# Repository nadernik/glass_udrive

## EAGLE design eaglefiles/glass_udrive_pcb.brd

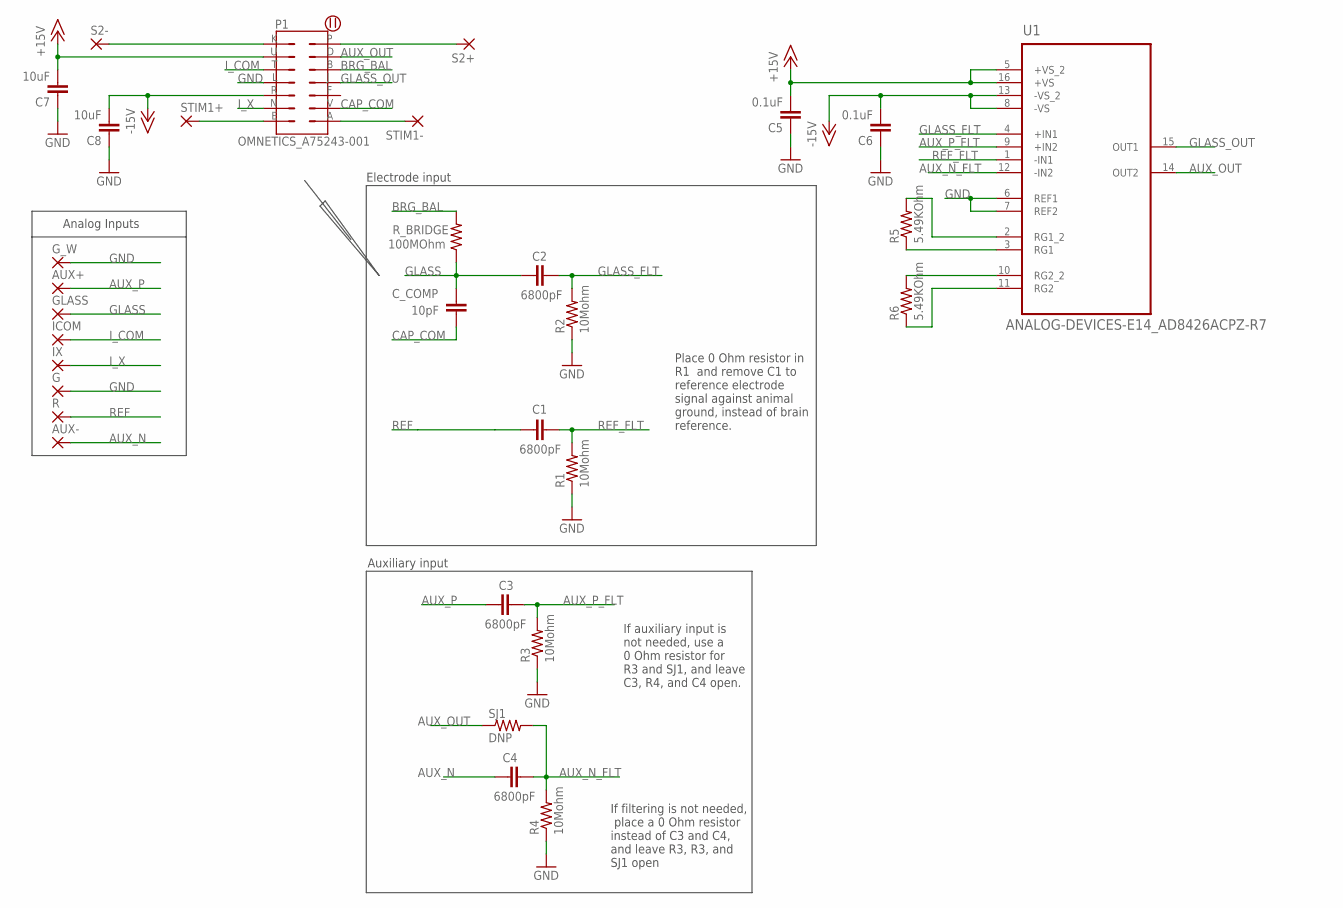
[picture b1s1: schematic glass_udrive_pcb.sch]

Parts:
AUX+: THROUGH-HOLE-30MIL/15MIL; 30MIL/15MIL
AUX-: THROUGH-HOLE-30MIL/15MIL; 30MIL/15MIL
C1, C2, C3, C4: 6800pF; 0201
C5, C6: 0.1uF; 0201
C7, C8: 10uF; 0603
C_COMP: 10pF; 0402
G: THROUGH-HOLE-30MIL/15MIL; 30MIL/15MIL
GLASS: THROUGH-HOLE-30MIL/15MIL; 30MIL/15MIL
G_W: THROUGH-HOLE-30MIL/15MIL; 30MIL/15MIL
ICOM: THROUGH-HOLE-30MIL/15MIL; 30MIL/15MIL
IX: THROUGH-HOLE-30MIL/15MIL; 30MIL/15MIL
P1: OMNETICS_A75243-001
R: THROUGH-HOLE-30MIL/15MIL; 30MIL/15MIL
R1, R2, R3, R4: 10Mohm; 0201
R5, R6: 5.49KOhm; 0201
R_BRIDGE: 100MOhm; 0402
S2+, S2-: THROUGH-HOLE-30MIL/15MIL; 30MIL/15MIL
SJ1: DNP; 0201
STIM1+, STIM1-: THROUGH-HOLE-30MIL/15MIL; 30MIL/15MIL
U1: ANALOG-DEVICES-E14_AD8426ACPZ-R7; ANALOG-DEVICES-E14_QFN65P400X400X100-16N

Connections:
+15V: C5.2, C7.2, P1.U, U1.5 (+VS_2), U1.16 (+VS)
-15V: C6.2, C8.2, P1.R, U1.8 (-VS), U1.13 (-VS_2)
AUX_N: AUX-.P$1, C4.1
AUX_N_FLT: C4.2, R4.2, SJ1.2, U1.12 (-IN2)
AUX_OUT: P1.D, SJ1.1, U1.14 (OUT2)
AUX_P: AUX+.P$1, C3.1
AUX_P_FLT: C3.2, R3.2, U1.9 (+IN2)
BRG_BAL: P1.B, R_BRIDGE.2
CAP_COM: C_COMP.2, P1.V
GLASS: C2.1, C_COMP.1, GLASS.P$1, R_BRIDGE.1
GLASS_FLT: C2.2, R2.2, U1.4 (+IN1)
GLASS_OUT: P1.J, U1.15 (OUT1)
GND: C5.1, C6.1, C7.1, C8.1, G.P$1, G_W.P$1, P1.L, R1.1, R2.1, R3.1, R4.1, U1.6 (REF1), U1.7 (REF2)
I_COM: ICOM.P$1, P1.T
I_X: IX.P$1, P1.N
unnamed: R5.2, U1.2 (RG1_2)
unnamed: R5.1, U1.3 (RG1)
unnamed: R6.2, U1.10 (RG2_2)
unnamed: R6.1, U1.11 (RG2)
REF: C1.1, R.P$1
REF_FLT: C1.2, R1.2, U1.1 (-IN1)
STIM1_N: P1.A, STIM1-.P$1
STIM1_P: P1.E, STIM1+.P$1
STIM2_N: P1.P, S2+.P$1
STIM2_P: P1.K, S2-.P$1

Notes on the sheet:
Analog Inputs
Electrode input
Auxiliary input
Place 0 Ohm resistor in R1 and remove C1 to reference electrode signal against animal ground, instead of brain reference.
If auxiliary input is not needed, use a 0 Ohm resistor for R3 and SJ1, and leave C3, R4, and C4 open.
If filtering is not needed, place a 0 Ohm resistor instead of C3 and C4, and leave R3, R3, and SJ1 open

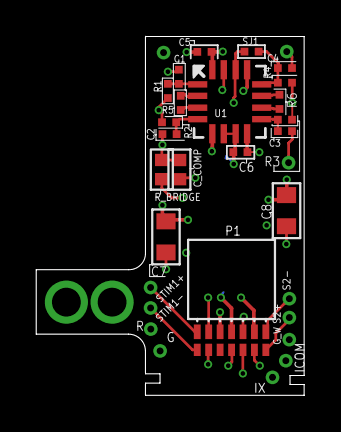
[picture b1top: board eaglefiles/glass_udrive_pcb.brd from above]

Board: 4 copper layers, 14.9 x 19.9 mm, 31 parts (0 on the bottom side), 25 nets.

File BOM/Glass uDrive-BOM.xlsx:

Part on PCB | QTY | Value | Device | Package | Description | Use | SUPPLIER | partNo | link
U1 | 1.0 | AD8224ACPZ-R7 | AD8224 | QFN65P400X400X100-16N | IC OPAMP INSTR 1.5MHZ 16LFCSP-Hidden pad | Wide Supply Range, Rail-to-Rail Output Instrumentation Amplifier | Analog Devices | AD8224HBCPZ-R7CT-ND | https://www.digikey.com/short/jmmmcj
P1 | 1.0 | A75243-001 | A75243-001 | OMNETICS_A75243-001 |  | 14 pin nano, male | Omnetics | A75243-001
R_BRIDGE | 1.0 | 100MOhm | R_0402 | 402.0 | RES 100M OHM 5% 1/16W 0402 | Resistor for bridge balance circuit | Stackpole Electronics Inc | HMC0402JT100MCT-ND | https://www.digikey.com/product-detail/en/stackpole-electron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
C_COMP | 1.0 | 10pF | C_0402 | 402.0 | CAP CER 10PF 200V C0G/NP0 0402 | Capacitor for capacitance neutralization circuit | American Technical Ceramics | 1284-1096-1-ND | https://www.digikey.com/short/j4081m
C1-C4 | 4.0 | 6800pF | C_0201 | 201.0 | CAP CER 6800PF 16V X7R 0201 | Capacitor for high pass filter for electrodes and virtual ground (with R1-R4) | TDK Corporation | 445-12081-1-ND | http://www.digikey.com/short/38852m
C5-C6 | 2.0 | 0.1uF | C_0201 | 201.0 | CAP CER 0.1UF 25V X5R 0201 | Bypass capacitor for INA | Samsung Electro-Mechanics | 1276-1318-1-ND | https://www.digikey.com/short/jmmm1h
C7-C8 | 2.0 | 10uF | R_0603 | 603.0 | CAP CER 10UF 25V X5R 0603 | Bypass big capacitor for +-15 V supply for INA | Murata Electronics | 490-10991-2-ND | https://www.digikey.com/short/j403zm
R1-R4 | 4.0 | 10Mohm | R_0201 | 201.0 | RES SMD 10M OHM 5% 1/20W 0201 | Resistor for high pass filter for electrodes and virtual ground (with C1-C4) | Samsung Electro-Mechanics | 1276-3857-1-ND | https://www.digikey.com/short/jmm95b
R5-R6 | 1.0 | 5.49KOhm | R_0201 | 201.0 | RES SMD 5.49K OHM 1/20W 0201 | Gain setting resistor for INA (gain=10) | Panasonic Electronic | P121609CT-ND | https://www.digikey.com/short/j40jpz
SJ1 | 4.0 | 0 Ohm | R_0201 | 201.0

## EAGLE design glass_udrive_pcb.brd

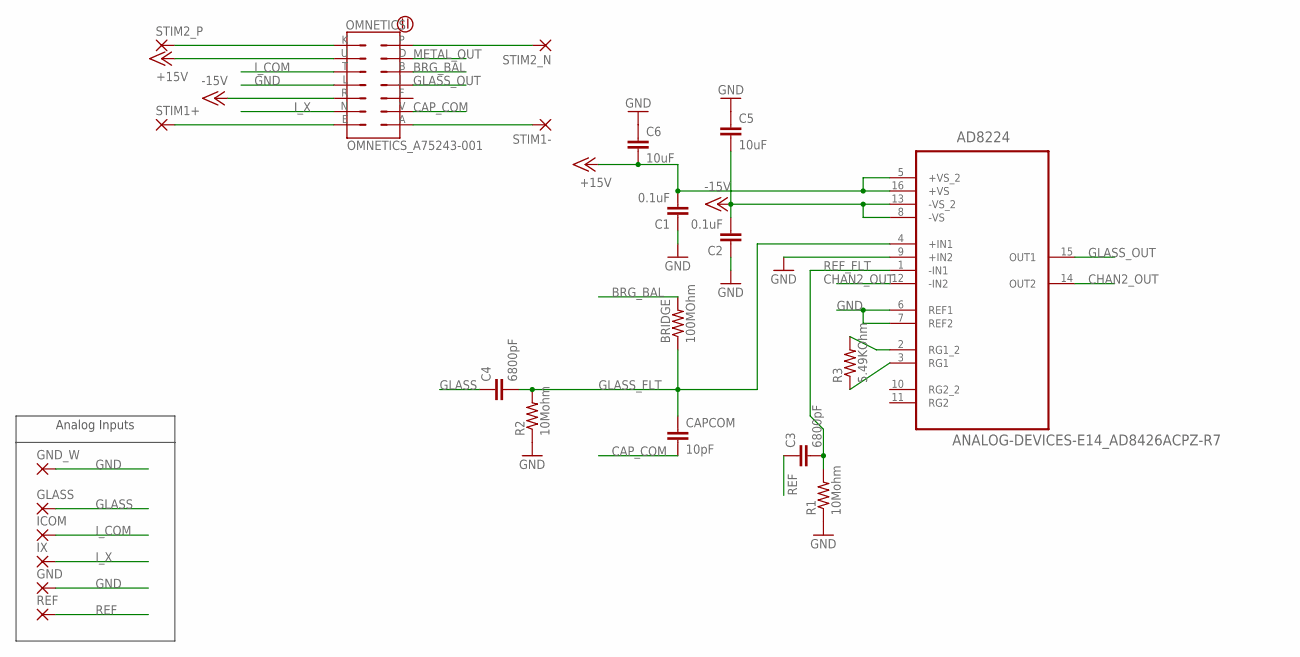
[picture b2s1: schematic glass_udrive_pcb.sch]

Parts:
AD8224: ANALOG-DEVICES-E14_AD8426ACPZ-R7; ANALOG-DEVICES-E14_QFN65P400X400X100-16N
BRIDGE: 100MOhm; 1206
C1, C2: 0.1uF; 0201
C3, C4: 6800pF; 0201
C5, C6: 10uF; 0603
CAPCOM: 10pF; 0402
GLASS: THROUGH-HOLE-30MIL/15MIL; 30MIL/15MIL
GND: THROUGH-HOLE-30MIL/15MIL; 30MIL/15MIL
GND_W: THROUGH-HOLE-30MIL/15MIL; 30MIL/15MIL
ICOM: THROUGH-HOLE-30MIL/15MIL; 30MIL/15MIL
IX: THROUGH-HOLE-30MIL/15MIL; 30MIL/15MIL
OMNETICS: OMNETICS_A75243-001
R1, R2: 10Mohm; 0201
R3: 5.49KOhm; 0201
REF: THROUGH-HOLE-30MIL/15MIL; 30MIL/15MIL
STIM1+, STIM1-, STIM2_N, STIM2_P: THROUGH-HOLE-30MIL/15MIL; 30MIL/15MIL

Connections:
+15V: AD8224.5 (+VS_2), AD8224.16 (+VS), C1.2, C6.2, OMNETICS.U
-15V: AD8224.8 (-VS), AD8224.13 (-VS_2), C2.2, C5.2, OMNETICS.R
BRG_BAL: BRIDGE.2, OMNETICS.B
CAP_COM: CAPCOM.2, OMNETICS.V
CHAN2_OUT: AD8224.12 (-IN2), AD8224.14 (OUT2)
GLASS_OUT: AD8224.15 (OUT1), OMNETICS.J
GND: AD8224.6 (REF1), AD8224.7 (REF2), AD8224.9 (+IN2), C1.1, C2.1, C5.1, C6.1, GND.P$1, GND_W.P$1, OMNETICS.L, R1.1, R2.1
I_COM: ICOM.P$1, OMNETICS.T
I_X: IX.P$1, OMNETICS.N
METAL_OUT: OMNETICS.D
unnamed: AD8224.2 (RG1_2), R3.2
unnamed: AD8224.3 (RG1), R3.1
REF: C3.1, REF.P$1
REF_FLT: AD8224.1 (-IN1), C3.2, R1.2
STIM1_N: OMNETICS.A, STIM1-.P$1
STIM1_P: OMNETICS.E, STIM1+.P$1
STIM2_N: OMNETICS.P, STIM2_N.P$1
STIM2_P: OMNETICS.K, STIM2_P.P$1

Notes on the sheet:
Analog Inputs

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
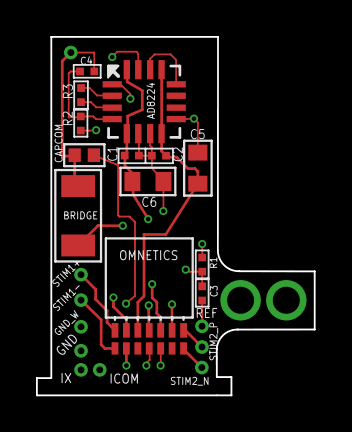
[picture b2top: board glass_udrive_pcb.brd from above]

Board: 4 copper layers, 15.4 x 19.9 mm, 23 parts (0 on the bottom side), 19 nets.

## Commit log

2018-04-24 :original commit adding PCB design files
2018-04-24 smashed labels
2018-04-25 Galen's suggested changes to Rev 1.0
    I have changed a number of things in your design, one of which is major and the
    rest are minor. The major change is that I have added a guard trace to your
    design, in accordance with the data sheet for the OPA129. If you are going to
    use an ultra-low input bias current op amp, then you should make efforts to
    actually achieve the performance that it touts. The other changes are mostly
    positioning to accommodate the guard trace, changes to the silk screen on your
2018-04-25 3D snapshots and Galen's edits merged.
2018-04-30 added data sheets for AD8224
2018-05-03 Revision AD8224 redesigned to use instrumentation amplifier with a reference electrode. This version has 2 input and 2 INA output channels one for glass electrode and another for a metal electrode.
2018-05-03 the modified version w/o output channel 2 and metal electrode input.
2018-05-07 1-Incorporating Michael Stetner's comments: ====================================================== 1. Move vias carrying output signals away from the corners of the AD8224. According to the datasheet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
2018-05-07 extended drive length to give more space at the bottom for dental cement anchoring. PCB = 9.26mm X 19.91 mm
2018-05-07 solved the order of CAPCOM and Bridge balance nets and routing as per GFL suggestions.
2018-05-07 minor routing and dimension and docu layer changes.
2018-05-08 Remove temporary and useless files
2018-05-08 Improve .gitignore to prevent inclusion of autorouter files
2018-05-08 Move eagle design files into separate directory
2018-05-08 Add gerbers dir to project, which should be empty
2018-05-08 Move layouyt files to their own directory
2018-05-08 Remove screenshots from repo
    These screen shots are 'derived' from the design files and should not be in the
    repository itself. For example, are they currently up to date, or do they
    reflect the design as it was a few commits ago? It's hard to tell, and therefore
    I think these sorts of files do more harm than good.
2018-05-09 Dev branches merged into master branch. Optimizing the board routing and incorporating GFL comments: =========================== 1- top right of AD8224 (pins 12 and 13): don't run a trace under the c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
2018-05-09 stuff and things
2018-05-10 updated several board layout details: made it smaller H and W, changed the anchoring tab on the opposite side, added +-15 power supply pours to simplify routing and reduced bridge resistor size to 40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
2018-05-11 Move bridge balance resistor up and trace from glass electrode to CAPCOM to layer 15
2018-05-11 Added optional circuit for 2nd INA channel and routing optimized.
2018-05-13 simple routing finish-up and silk-screen stuff.
2018-05-13 Went very OCD on your design
    Made the power planes bigger because they had no reason not to be.
    Renamed some nets because I found them confusing when looking at your schematic.
    Moved stuff for cleaner routing.
    Added a top ground plane to prevent stray capacitance onto any moving wires for
    your electrode etc.
    Improved via placement on bypass capacitors.
2018-05-14 Made glass net more compact.
    Silk screen needs a lot of work
2018-05-14 improvements on slikscreen and component naming and placing.
2018-05-14 final touch by NN.
2018-05-21 minor routing and dimention and docu layer improvements.
2018-05-23 gerber files generated.
2018-05-24 minor edits to board layout, moved vias from under the motor, increased trace width to 6mil and above. GALEN CHECKED after Stetner checked!
